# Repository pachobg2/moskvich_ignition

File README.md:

# moskvich_ignition — programmable ignition ECU for the Moskvich 412 / 2140

ESP32-C3 replaces the points-and-coil ignition's *switching* job while keeping
the original distributor. The points become a crank-position sensor, the ECU
fires the coil through an IGBT at a timing it looks up from an **rpm × MAP
map**, controls dwell from battery voltage, trims idle speed with spark
timing, and limits revs. Everything is tuned from a phone over the ECU's own
WiFi network — no app to install, no router needed.

> **Experimental, safety-relevant.** Wrong spark timing can wreck an engine,
> and a dead ECU means a dead engine (see *Limitations*). Bench-test with the
> simulator, verify timing with a timing light before every first start, and
> start from the conservative default map.

## How it works

```
 12 V switched ──┬── protection + buck ──► ESP32-C3 ──► gate ──► IGBT ──► coil (−)
                 │                           ▲  ▲
 distributor ────┼── pull-up + NPN ──────────┘  │ ADC
   (points)      │                              │
 MAP hose ───────┴── MPX4115-class sensor ──────┘
```

* **Trigger reference (Setup):** two choices.
  **OPEN edge (default)** — distributor locked at full advance, trigger ≈ 40°: most accurate.
  **CLOSE edge** — factory distributor (weights blocked at rest, vacuum capsule off), trigger ≈ 120°
  before the firing cylinder: the ECU predicts ~3× further ahead (use *Acceleration compensation*
  100%, which the UI sets for you), and while cranking it falls back to the OPEN edge (≈10° factory
  static timing) because 120° of prediction is far too coarse at cranking-speed variation.
  Host-simulated error: ≤0.04° steady, ~0.9° over a 1000→5500 rpm/4 s ramp, ≤0.5° on a hard
  lift-off with compensation, ≈0.3° cranking. The closing edge bounces more than the opening one:
  verify on a scope.
* **Points = sensor only.** They no longer carry coil current (no arcing, no
  condenser needed). The instant they *open* marks a fixed crank angle,
  `trigger angle` (≈ 40° BTDC).
* **The distributor's mechanical advance is locked at that angle** (weights
  blocked, vacuum capsule disconnected). The ECU can only *delay* the spark
  relative to the trigger, so any advance up to the trigger angle is
  available:
  `delay = (trigger − target advance) / 180° × time since last trigger`.
* **Dwell** is ECU-controlled and voltage-compensated: at idle/cranking the
  coil is switched on `delay − dwell` after the trigger (exact dwell); at
  higher rpm it is scheduled one cycle ahead from the measured period.
* **Timing map**: 16 rpm × 16 MAP bins, bilinear interpolation, ± idle trim,
  rev-limit retard, slew limit per spark, min/max clamps.
* **LPG**: a 12 V signal from the LPG valve (GPIO3 via divider) switches the
  timing. Two modes (LPG tab): **static offset** (petrol map + N degrees,
  default +3°; no map is shown) or a **separate LPG map** (edited on the LPG tab, with
  *Copy petrol → LPG* and an optional offset). The change is slewed in at the normal per-spark limit,
  never stepped. A *Force petrol / Force LPG* override in Setup helps testing without
  the valve connected (LPG tab).
* **Factory-derived maps (Map tab → "Ignition map")**: besides your *Custom* map there are three
  slots built from the distributor data tables of the UZAM-412 family — **P-147A**, **47.3706**,
  **P-147B** — so the engine can run on a replica of the original advance curve and you can tune from there.
  Total advance = static timing + centrifugal(rpm) + vacuum(MAP) × fade(rpm), using the data-sheet
  centrifugal points (1000–5000 rpm) and the vacuum-capsule points (mmHg). Assumptions: the static
  timing is 10° (editable, "Regenerate"); the tables are in crank degrees; vacuum = 101.3 kPa − MAP;
  the capsule's tolerance bands are used at their middle; the capsule is fed from a *ported* carburettor
  vacuum that is ~0 at idle, so the vacuum advance fades in between 900 and 1300 rpm; centrifugal advance
  starts at 600 rpm and stays at its 5000 rpm value above that. **The curves reach 50–60°**, so the
  trigger angle and *Maximum advance* must allow it (the CLOSE-edge reference at ≈120° does; a 30–40° trigger
  clips them — the app shows how many cells are clipped and hatches them). You can edit a factory slot;
  *Regenerate* restores its factory curve and *Copy to Custom* starts a tune from it.
* **Cranking** uses a fixed retarded advance below `crank rpm`.
* **Rev limiter**: retard ramp from the soft limit, spark cut above the hard limit.
* **Idle control**: PI loop that nudges timing to hold the target idle rpm
  while the throttle is closed (MAP below a threshold).
* **Ignition ISRs run at interrupt priority 3**, above WiFi, so tuning on a
  phone does not move the spark. Flash writes (saving, OTA) *do* stall them,
  so the ECU **refuses to write flash while the engine turns** — edits apply
  live and are saved when you press Save with the engine stopped, or
  automatically when it stops.
* Hardware safeguards in firmware: coil-on watchdog (9 ms) if no spark was
  scheduled, no spark without a valid period measurement, bounce rejection,
  all inputs from the web app clamped by `sanitize()`.

## Files

| File | Purpose |
|---|---|
| `moskvich_ignition.ino` | setup/loop: ADC sampling, idle PI, LED, WiFi AP, OTA |
| `ignition_core.h` | **all ignition math & scheduling** — pure C++, no Arduino; tested on a PC |
| `ecu_engine.h` | ESP32-C3 layer: GPIO ISR, two one-shot hardware timers, bench simulator |
| `ecu_store.h` | NVS persistence (checksummed) and parameter `sanitize()` |
| `ecu_web.h` | web server + JSON API |
| `web/index.html` | the tuning app (single file, no dependencies; add `?mock` to try it on a PC) |
| `web_ui.h` | generated from `web/index.html` by `python tools/embed_ui.py` |
| `test/test_core.cpp` | engine-model simulation of the real ISR logic |
| `config.h.example` | copy to `config.h`: AP/OTA passwords, pins, sensor constants (gitignored) |
| `docs/HARDWARE.md` | circuit, parts list, wiring, install & tuning procedure |
| `hardware/` | **schematic, PCB (KiCad), BOM** — through-hole, ESP32-C3-Zero, IGBT cut-out; see `hardware/README.md` |

## Build

Arduino IDE / arduino-cli, **esp32 core 3.x**, board *ESP32C3 Dev Module*
(*USB CDC On Boot: Enabled* for the SuperMini), library **ArduinoJson 7**.

```bash
arduino-cli compile --fqbn esp32:esp32:esp32c3:CDCOnBoot=cdc .
```

Copy `config.h.example` → `config.h` and set the passwords. After editing
`web/index.html` run `python tools/embed_ui.py`.

Host tests (any C++17 compiler):

```bash
c++ -O2 -std=c++17 -I. test/test_core.cpp -o test/test_core && ./test/test_core
```

## Using it

1. Join WiFi **Moskvich-ECU** (password from `config.h`); the app opens as a
   captive portal, or browse to `http://192.168.4.1`.
2. **Live** — rpm, advance, MAP, battery, dwell, 60 s chart.
3. **Map** — petrol map: tap cells, ±0.5/±1, Set, Smooth, Range select, Undo, editable axes.
   The cells around the current operating point glow while the engine runs.
4. **Setup** — trigger angle, cranking, idle, limits, dwell table, MAP sensor two-point calibration.
   **LPG** — mode, static offset or the separate LPG map, valve-signal status, override.
5. **Language** — the **БГ / EN** button in the header switches the whole interface between Bulgarian and English (remembered per browser; `?lang=bg` in the URL also works). The default follows the browser language. Translations live in the `BG` table in `web/index.html`; the firmware-upload page is bilingual.
6. **Tools** — timing-light lock, bench simulator, JSON backup/restore, reset, firmware update.

Install, wiring and the timing-light calibration procedure are in
[docs/HARDWARE.md](docs/HARDWARE.md).

## Limitations / ideas

* **No limp-home.** With advance locked at 40°, running the stock points
  circuit would kick back on starting, so there is no relay bypass. Carry a
  spare ECU or the original distributor internals.
* No cam/phase signal: cylinder-to-cylinder cam-lobe and bushing wear shows up as
  a few degrees of scatter that the ECU cannot correct. A Hall-effect or
  optical distributor conversion would use the same input (set the edge).
* No knock sensor, no coolant/air temperature correction (spare ADC pins exist).
* ISR jitter vs. WiFi has been reasoned about, not scope-measured: verify with a
  scope/timing light at 6000 rpm on the bench simulator and adjust `latency_us`.
* Idea: log a short ring buffer of rpm/MAP/advance for download after a drive.

## Version History

| Version | Date | Changes |
|---|---|---|
| 1.0.0 | 2026-10-26 | Initial release: points-trigger delay-only timing, 16×16 rpm×MAP map, voltage-compensated dwell, cranking/idle/rev-limit logic, WiFi AP web tuner (live data, map editor, setup, timing-light lock, bench simulator, backup, OTA), host-side engine-model tests. |
| 1.1.0 | 2026-10-27 | MAP sensor two-point calibration in Setup (any linear 1-bar analog sensor, e.g. GM/Lada/Bosch; capture-from-live-reading buttons); `MAP_SLOPE`/`MAP_OFFSET`/`MAP_SUPPLY_MV` removed from `config.h`. Stored settings from 1.0.0 are discarded on first boot (defaults load). |
| 1.2.0 | 2026-10-27 | LPG timing: 12 V valve-signal input (GPIO3, hysteresis + debounce), static-offset mode or separate LPG map, copy petrol → LPG (+offset), manual override, LPG badge in the UI. Settings from 1.1.0 are discarded on first boot (defaults load). |
| 1.2.1 | 2026-10-27 | UI: LPG settings moved to their own tab; the LPG map is only shown in "Separate LPG map" mode (static-offset mode shows just the offset). |
| 1.3.0 | 2026-10-27 | Setup: choice of trigger reference — points OPEN edge (distributor locked at full advance, ~40°) or points CLOSE edge (factory distributor, ~120°) with automatic OPEN-edge cranking reference; trigger angle range up to 160°; extended host tests. Settings from 1.2.x are discarded on first boot (defaults load). |
| 1.4.0 | 2026-10-27 | Web interface available in Bulgarian (БГ/EN switch, default from browser language), bilingual firmware-upload page; fix: elements marked hidden (e.g. the LPG copy button on the petrol map) were still shown. |
| 1.4.1 | 2026-10-27 | UI: hover tooltips (in both languages) on every setting and control, e.g. what Gain (P) and Gain (I) do; the web page is now stored gzip-compressed (flash use 92% -> 88%). |
| 1.5.0 | 2026-10-27 | Targets the ESP32-C3-Zero board (new PCB in `hardware/`): pins LPG 0 / MAP 1 / VBAT 3 / POINTS 4 / COIL 6, status shown on the on-board RGB LED (GPIO10). |
| 1.6.0 | 2026-10-28 | Three factory-derived petrol maps (P-147A, 47.3706, P-147B) selectable in the Map tab, built from the UZAM-412 distributor centrifugal + vacuum advance tables; regenerate / copy-to-custom; map cells may exceed the trigger angle (clipped at use, shown in the UI). Settings from 1.5.0 are discarded on first boot (defaults load). |
| 1.6.1 | 2026-10-28 | UI: switching the trigger reference to CLOSE edge now also raises Maximum advance to 60° (it was still capping the map at 38°); the "cells exceed the limit" warning names the limit that is binding (Maximum advance or Trigger angle) and where to change it. |
| 1.6.2 | 2026-10-28 | Safety: firmware updates are refused while the engine runs (a bare POST to /update no longer reboots the ECU, and ArduinoOTA is not serviced while running); /update reports OK only after a completed upload. |

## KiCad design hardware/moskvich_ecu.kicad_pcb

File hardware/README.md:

# ECU hardware — schematic, PCB, BOM (rev B, SMD)

A small two-sided board: **SMD** passives and ICs (0603 / 0805 / 1206 / 1210, SOT-23, SOIC-16, SMA/SMB), an
**SMD buck regulator** for the 5 V rail, an **ESP32-C3-Zero** on pin sockets, 3.5 mm screw terminals, and the
ignition **IGBT lying in a cut-out** so the case floor cools it. **48 × 41.8 mm** (about a third of the
through-hole rev A).

| File | What it is |
|---|---|
| `schematic.svg` | One-sheet schematic (open in any browser) |
| `pcb_top.svg`, `pcb_bottom.svg` | Board previews (both copper layers, courtyards, cut-out) |
| `moskvich_ecu.kicad_sch` | **Editable schematic**, KiCad 7 format (every pin has a net label; no hand-routed wires). Its netlist is checked identical to the PCB's. |
| `moskvich_ecu.kicad_pro` | Minimal KiCad project so the schematic and PCB open together |
| `moskvich_ecu.kicad_pcb` | The PCB, KiCad 7 format (footprints embedded, tracks, vias, GND pours, outline + cut-out) |
| `bom.csv`, `netlist.csv` | Parts list and net list |
| `gen/pcbgen.py` | Generator: parts, placement, auto-router, design-rule check, KiCad/SVG/BOM export |
| `gen/gen_schematic.py` | Draws `schematic.svg` (the readable picture) |
| `gen/gen_kicad_sch.py` | Writes `moskvich_ecu.kicad_sch` and verifies it against the PCB netlist |

Regenerate everything (needs `numpy scipy shapely`):

```bash
python hardware/gen/pcbgen.py && python hardware/gen/gen_schematic.py && python hardware/gen/gen_kicad_sch.py
```

> **Status — read this.** The board was generated and checked by my own script: copper clearance ≥ 0.2 mm
> (≥ 0.7 mm around the coil net), every net connected, nothing within 0.5 mm of the edge or inside the
> cut-out, no footprint overlaps, no hole collisions. The file parses in a KiCad-format library.
> **It has not been opened in KiCad, run through KiCad's DRC, or built.** The footprints are generic
> IPC-style land patterns I defined, not manufacturer drawings. Before ordering: open it in KiCad ≥ 7, press
> **B** to fill the zones, run **Inspect → Design Rules Checker**, and compare every footprint with the
> datasheet of the exact part you buy (especially the inductor, the fuse, the terminals and the module).

## Opening it in KiCad or EasyEDA

* **KiCad 7+:** open `moskvich_ecu.kicad_pro`. The schematic uses simple embedded symbols (boxes with named pins) and
  the footprint names of the PCB; reassign footprints/symbols to library parts as you like, then *Update PCB from schematic*.
* **EasyEDA:** import the files through EasyEDA's KiCad import (File → Import; menu names differ between the
  Standard and Pro editions — I have not tried it here). Import the schematic and the PCB; if the editor
  complains, open them in KiCad first and re-export. Replace the generic footprints with EasyEDA/LCSC library parts
  (this also gives JLCPCB assembly part numbers).
* The schematic is a **grouped parts-and-nets drawing**: connections are carried by net labels, not long wires.
  `schematic.svg` is the readable hand-arranged picture of the same circuit.
* Neither file was opened in KiCad/EasyEDA by me; the script re-reads the schematic and checks every pin's net
  against the PCB netlist (42 symbols, 24 nets, no mismatches).

## Circuit in one paragraph

Ignition-switched 12 V → 0.5 A fuse → SS34 Schottky (reverse polarity) → SMBJ24A TVS → 10 µF → **AP63205**
buck (3.8–32 V in, fixed 5 V, 2 A; L = 4.7 µH, 2 × 22 µF out, 100 nF boot — the datasheet's values) → 5 V. The
points signal (J1.1) is pulled up through 1 kΩ (wetting current), divided and inverted by a BC847 into GPIO4.
The LPG valve signal, the battery voltage and the MAP sensor each go through a divider with a 100 nF cap and
a 3.6 V zener into ADC1 pins. The MCU's coil command (GPIO6) feeds a **CD74HCT221** monostable that (a) turns the 3.3 V
logic into a 5 V gate drive and (b) limits coil-on time in hardware (≈ 16–23 ms with the 15 kΩ / 2.2 µF
network; the firmware limits it to 9 ms first), so a hung MCU can never leave the coil charged. It drives the
**ISL9V3040P3** ignition IGBT; its collector (the tab) is the coil negative (J1.4). Coil current never flows
through the buck or the sensor grounds: it uses the 1.5 mm top-layer collector track and the GND pours / J1.3.

## Board facts

* **48 × 41.8 mm**, 2 layers, 1.6 mm, three M2.5 mounting holes. Origin = top-left corner, X right, Y down (as in KiCad).
* Rules used: tracks 0.2 mm (signal) / 0.4 mm (power) / **1.5 mm** (collector), clearance 0.2 mm (0.7 mm around the collector net), vias 0.8 / 0.4 mm, GND pours on both layers. These are within normal 2-layer fab capabilities.
* **Top side:** module sockets, J1/J2, the IGBT pads, and the buck stage (U2, L1, C1–C4, C11, D1, D2, F1).
* **Bottom side:** everything else (dividers, points input, the CD74HCT221 and its resistors). The bottom parts sit in the 6 mm gap between the board and the case floor, so keep them ≤ 3 mm tall.
* **Terminals:** J2 (top right) = LPG signal, +5 V, MAP signal, GND. J1 (right) = points lead, +12 V, GND, coil −. The coil track and the GND pour handle the 4 A pulses; use ≥ 1 mm² wire on J1.3 / J1.4.
* The module's USB-C faces the **top** edge (2.2 mm from it).

## Mounting the IGBT through the cut-out

The IGBT is cooled by the **case floor**, which acts as the heat sink.

```
   box floor (aluminium) ─────────────────────────────  z = 0
        │     ┌ M3 screw into a tapped hole in the floor
   tab ─┴─ insulating pad (silicone, 0.25 mm) + shoulder washer
   TO-220 lies flat in the cut-out  ───►  leads bent UP through the 3 pads
   PCB on 6 mm standoffs  ─────────────────────────────  z = 6
```

* **Cut-out:** 18.0 × 13.0 mm window at x 3.64 … 21.64, y 27.79 … 40.79 (bottom-left of the board). The strip below it is only 1.0 mm wide — handle the board by the edges.
* **Lead pads** (Q1), 3.0 mm to the right of the window, 2.54 mm pitch, 1.0 mm drill: collector (24.64, 34.29), emitter (24.64, 31.75), gate (24.64, 36.83) — the part is rotated 180° compared with a part lying leads-left, so **the gate is the lowest pad**. The silkscreen outline shows the package.
* **Tab hole** ends up near (8.1, 34.3) (the board is the drilling template through the cut-out). Check against your real part before drilling the floor.
* **Lead forming:** leave ~4 mm flat from the package, bend up 90°, trim to just clear the board top.
* **The tab is the coil negative** (battery voltage plus spikes to ~400 V). Insulate it from the case: silicone pad + plastic shoulder washer under the screw head. Check with a multimeter that tab ↔ case is open before powering the board.
* Dissipation is ≈ 2–3 W at 6000 rpm (≈ 0.3 W at idle); the floor of a metal box is plenty. On a plastic box use a real heat sink bolted to the tab.
* Conformal-coat the board: the collector net sees ~400 V flyback spikes with only 0.7–0.8 mm clearance.

## Parts and where the numbers come from

| Item | Notes |
|---|---|
| **AP63205WU-7** (U2) | Pinout, 4.7 µH / 10 µF / 2 × 22 µF / 100 nF and "EN to VIN" are from the Diodes datasheet (DS41326). Abs. max VIN 35 V DC / 40 V for 400 ms — hence the SMBJ24A TVS (clamps ≈ 39 V). Fit enough ceramic capacitance after derating (X7R/X5R lose capacity with DC bias). |
| **L1** | Any shielded 4.7 µH inductor, I_sat ≥ 2 A, DCR < 100 mΩ, about 4 × 4 mm. The land pattern is generic: adjust it to your part. |
| **F1** | An SMD fuse (0.5 A, ≥ 32 V rating) or a PTC of the same 1206 size. Ordinary 1206 PTCs are often rated only 6–15 V: do not use those. |
| **C10 / R14** | 2.2 µF X7R + 15 kΩ ⇒ guard time ≈ 0.7·R·C (CD74HCT221 datasheet), with the capacitor derated by its DC bias: 16–23 ms. If you change them keep it above the firmware's 9 ms and below ~25 ms. |
| ESP32-C3-Zero pad order | Pad numbers/GPIOs follow the Waveshare list (1 = 5V, 2 = GND, 3 = 3V3, 4–9 = IO0…IO5 down the left side, 10–18 = IO6, IO7, IO8, IO9, IO10, IO18, IO19, IO20, IO21 up the right side, USB at the top). **Read the silkscreen on your module** and measure the header row distance (15.24 mm assumed). |
| Module antenna | I did not leave a copper-free zone under the module (SMD parts and pours sit under its body); check where the antenna is on your revision and, if needed, move parts and add a keep-out there. |
| MAP sensor connector | J2.2 +5 V, J2.3 signal, J2.4 GND. GM-style sensors are usually A = ground, B = signal, C = 5 V — check yours. |

## Bring-up

1. **Without** the module, the CD74HCT221 and the IGBT: power from a bench supply (current limit 0.3 A). Check +5 V, check reverse polarity is blocked, check the TVS does not conduct at 14.4 V.
2. Fit U3 and the module, flash, join `Moskvich-ECU`. LED: blue blip = stopped, yellow = cranking, green = petrol, cyan = LPG, violet = simulator / OTA.
3. Tools → Bench simulator at 800 / 3000 / 6000 rpm with a **100 Ω resistor and LED, or a scope, instead of the coil** on J1.4. Check one pulse per trigger and on-time = the dwell shown in the Live tab.
4. Hold the command high on purpose (firmware stopped, jumper 3.3 V → GPIO6): the CD74HCT221 output must drop after ≈ 16–23 ms.
5. Only then fit Q1, connect the coil and the distributor, and follow `docs/HARDWARE.md`.

## Not done / ideas

* No gerbers: export them from KiCad (File → Plot) after the DRC. Add a fab note and silk text.
* Hand-soldering: everything is 0603 or larger; the SOIC-16 and TSOT-23-6 need a fine tip and flux. Solder the buck IC and its caps first, then check the 5 V rail.
* A coil-current sense resistor and an IGBT over-current limit were left out to keep the build simple.
* Unused module pins on the left header (IO2, IO5) are unconnected — a coolant-temperature divider would use IO2 (ADC1).

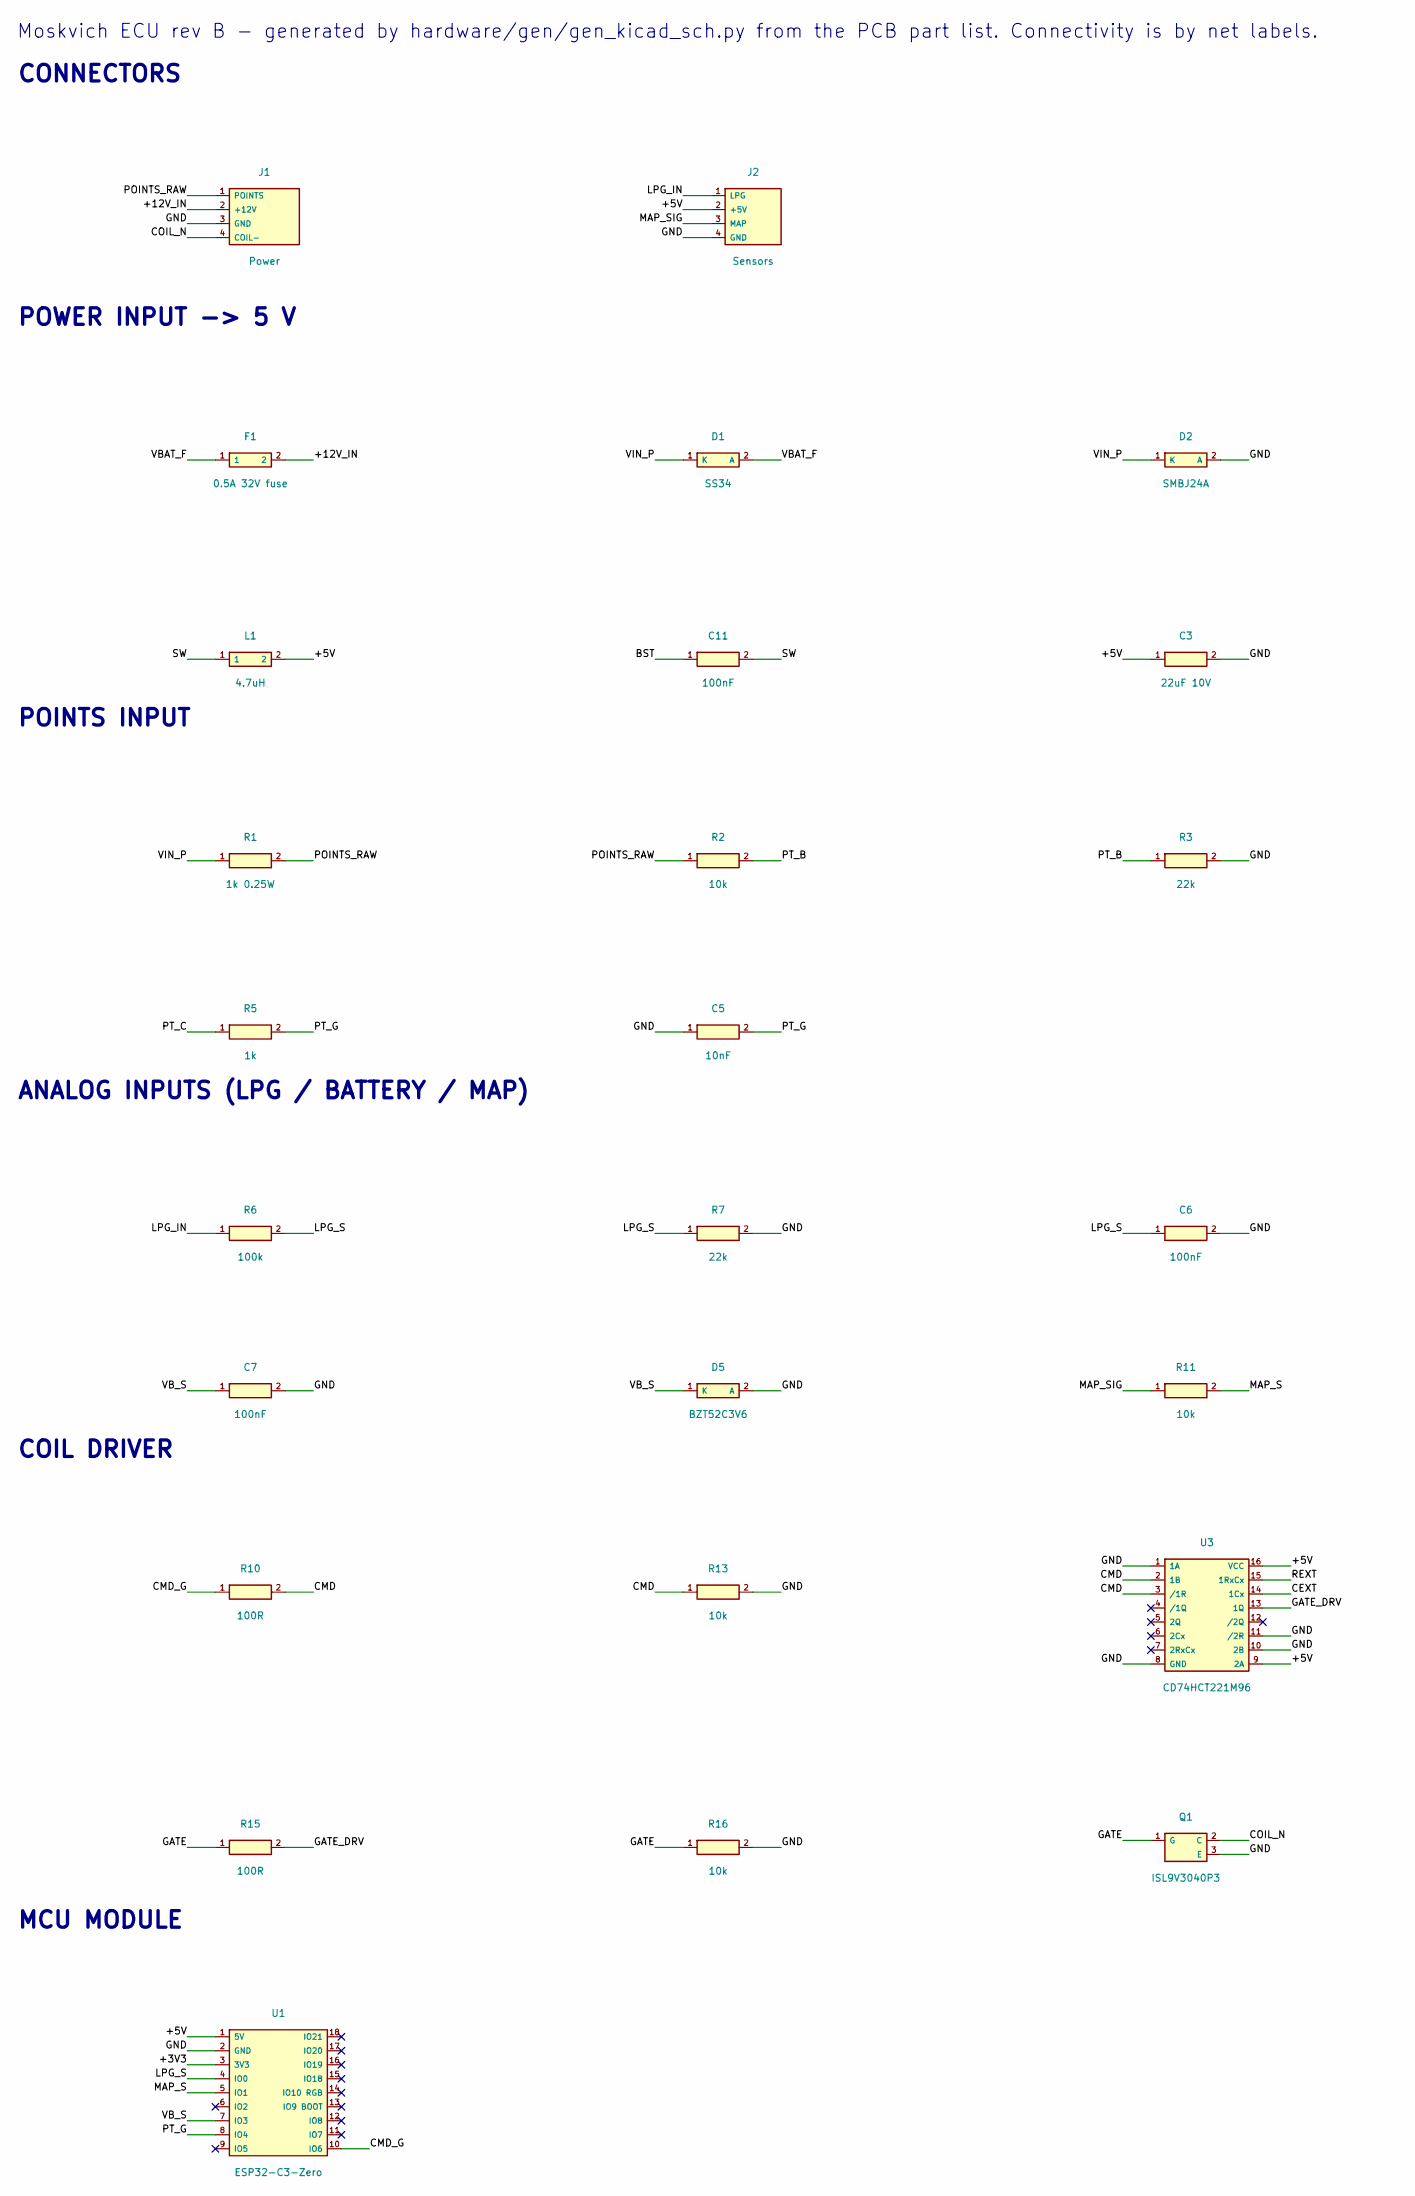
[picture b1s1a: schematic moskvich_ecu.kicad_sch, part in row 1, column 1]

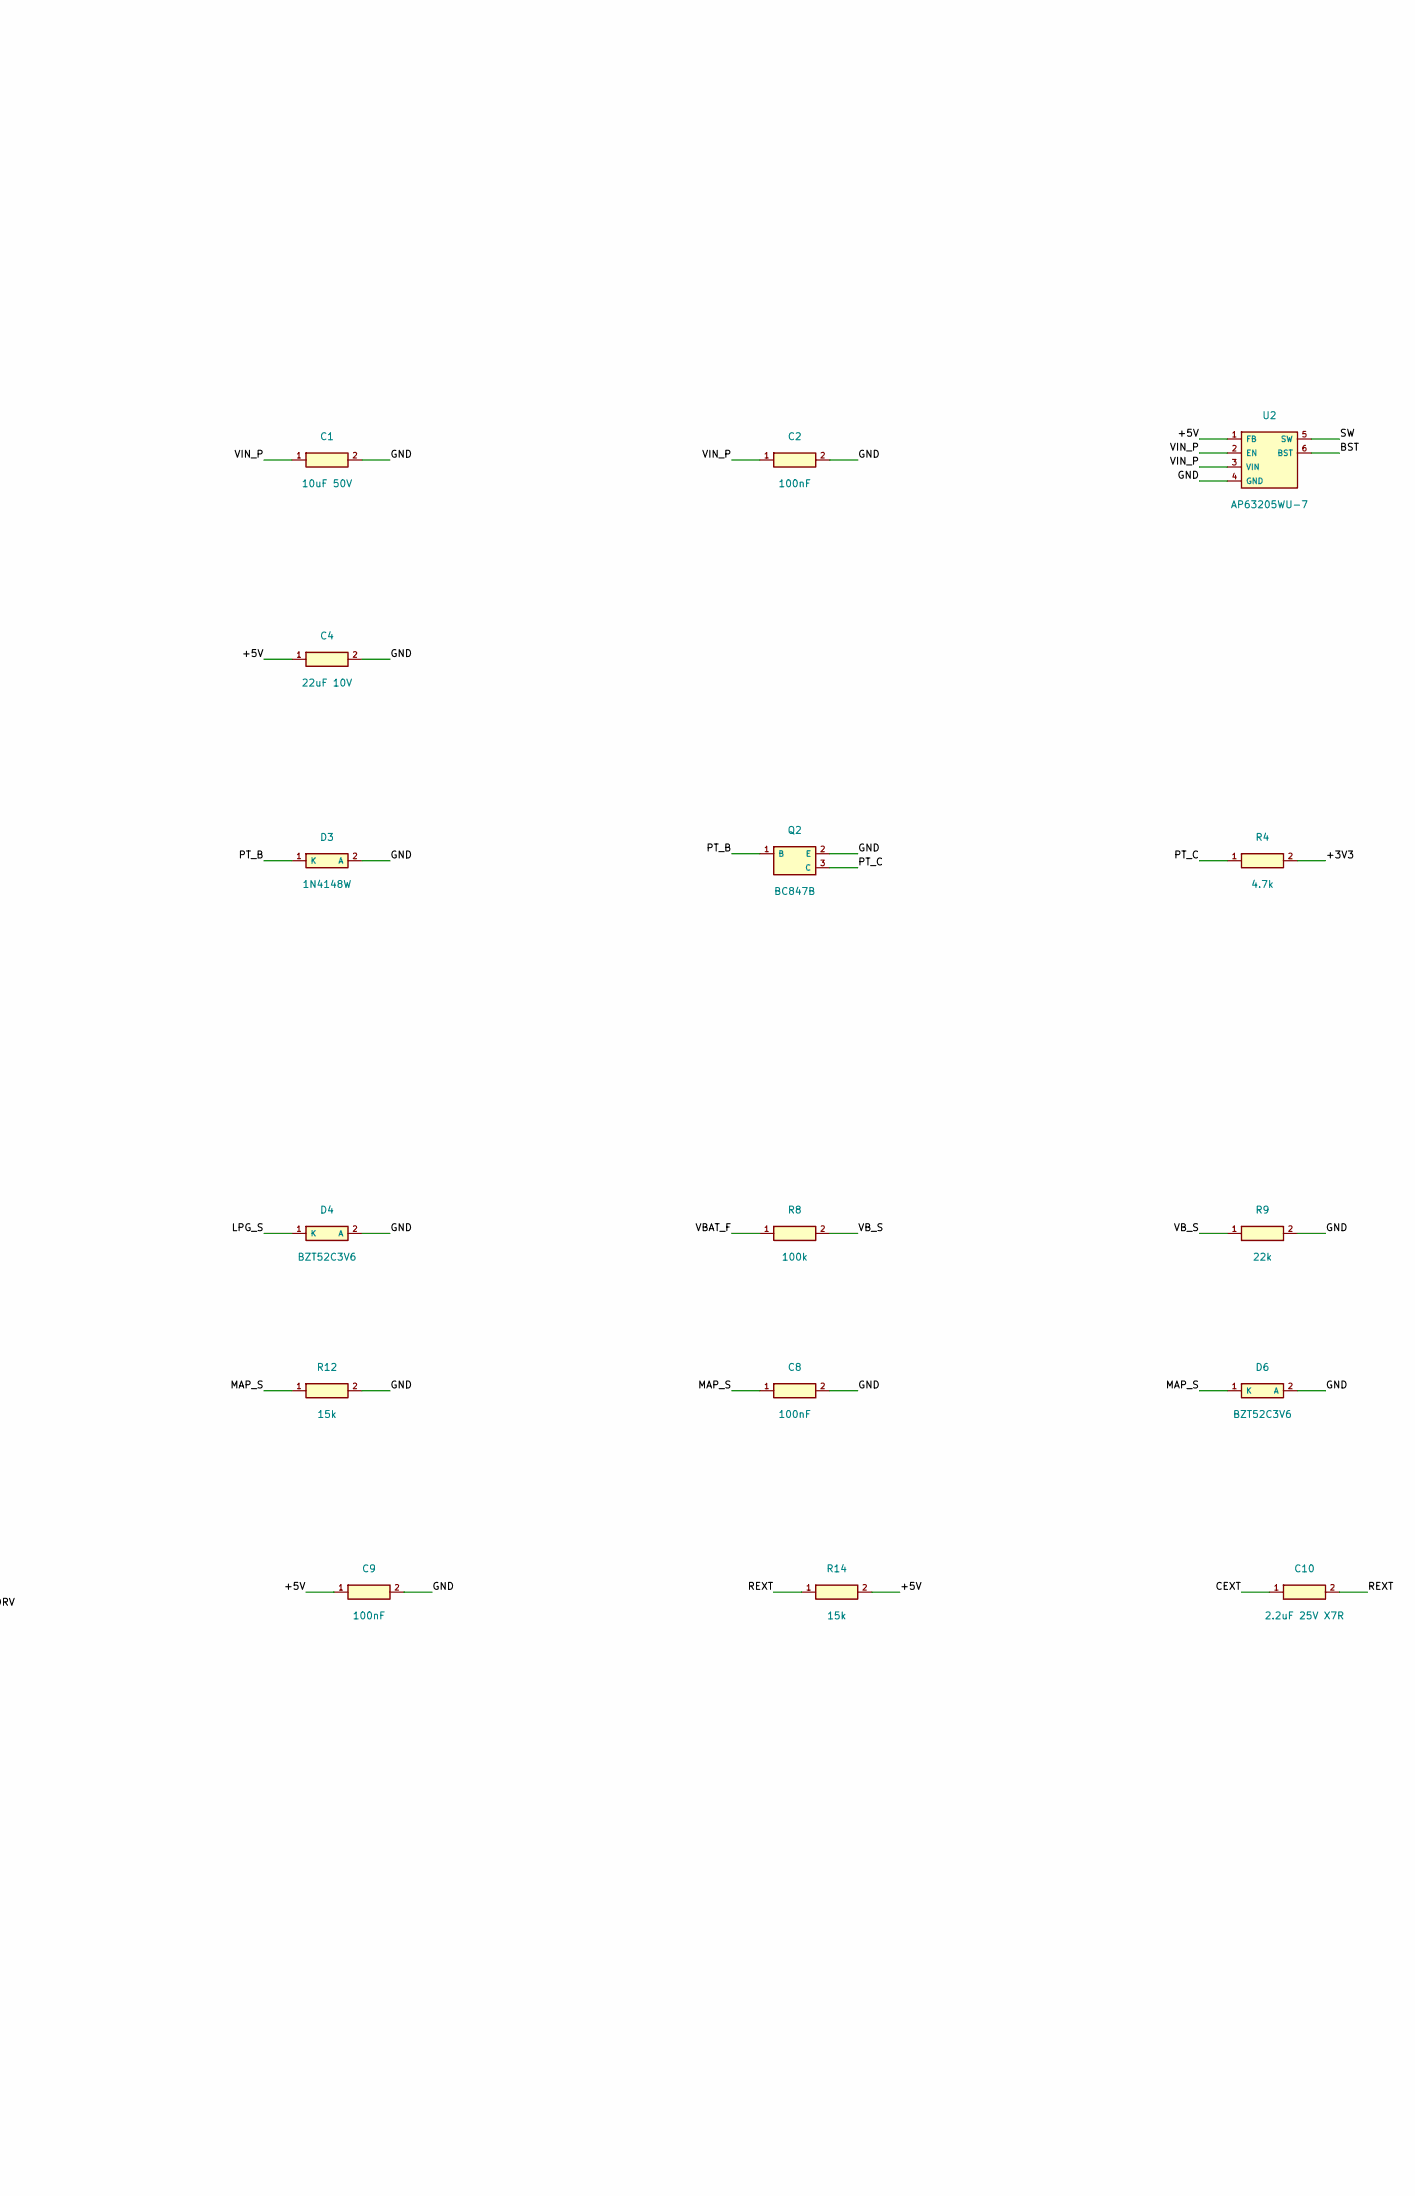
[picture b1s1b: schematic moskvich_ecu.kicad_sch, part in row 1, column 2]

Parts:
C1: 10uF 50V; C_1210_3225Metric
C2, C6, C7, C8, C9, C11: 100nF; C_0603_1608Metric
C3, C4: 22uF 10V; C_0805_2012Metric
C5: 10nF; C_0603_1608Metric
C10: 2.2uF 25V X7R; C_0805_2012Metric
D1: SS34; D_SMA
D2: SMBJ24A; D_SMB
D3: 1N4148W; D_SOD-123
D4, D5, D6: BZT52C3V6; D_SOD-123
F1: 0.5A 32V fuse; Fuse_1206_3216Metric
J1: Power; TerminalBlock_P3.50_1x04
J2: Sensors; TerminalBlock_P3.50_1x04
L1: 4.7uH; pick your inductor)
Q1: ISL9V3040P3; TO-220_LayDown_Cutout
Q2: BC847B; SOT-23
R1: 1k 0.25W; R_1206_3216Metric
R2, R11, R13, R16: 10k; R_0603_1608Metric
R3, R7, R9: 22k; R_0603_1608Metric
R4: 4.7k; R_0603_1608Metric
R5: 1k; R_0603_1608Metric
R6, R8: 100k; R_0603_1608Metric
R10, R15: 100R; R_0603_1608Metric
R12, R14: 15k; R_0603_1608Metric
U1: ESP32-C3-Zero; ESP32-C3-Zero_2x9_Socket
U2: AP63205WU-7; SOT-23-6
U3: CD74HCT221M96; SOIC-16_3.9x9.9mm_P1.27mm

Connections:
+3V3: R4.2, U1.3 (3V3)
+5V: C3.1, C4.1, C9.1, J2.2 (+5V), L1.2, R14.2, U1.1 (5V), U2.1 (FB), U3.9 (2A), U3.16 (VCC)
+12V_IN: F1.2, J1.2 (+12V)
BST: C11.1, U2.6 (BST)
CEXT: C10.1, U3.14 (1Cx)
CMD: R10.2, R13.1, U3.2 (1B), U3.3 (/1R)
CMD_G: R10.1, U1.10 (IO6)
COIL_N: J1.4 (COIL-), Q1.2 (C)
GATE: Q1.1 (G), R15.1, R16.1
GATE_DRV: R15.2, U3.13 (1Q)
GND: C1.2, C2.2, C3.2, C4.2, C5.1, C6.2, C7.2, C8.2, C9.2, D2.2 (A), D3.2 (A), D4.2 (A), D5.2 (A), D6.2 (A), J1.3 (GND), J2.4 (GND), Q1.3 (E), Q2.2 (E), R3.2, R7.2, R9.2, R12.2, R13.2, R16.2, U1.2 (GND), U2.4 (GND), U3.1 (1A), U3.8 (GND), U3.10 (2B), U3.11 (/2R)
LPG_IN: J2.1 (LPG), R6.1
LPG_S: C6.1, D4.1 (K), R6.2, R7.1, U1.4 (IO0)
MAP_S: C8.1, D6.1 (K), R11.2, R12.1, U1.5 (IO1)
MAP_SIG: J2.3 (MAP), R11.1
POINTS_RAW: J1.1 (POINTS), R1.2, R2.1
PT_B: D3.1 (K), Q2.1 (B), R2.2, R3.1
PT_C: Q2.3 (C), R4.1, R5.1
PT_G: C5.2, R5.2, U1.8 (IO4)
REXT: C10.2, R14.1, U3.15 (1RxCx)
SW: C11.2, L1.1, U2.5 (SW)
VBAT_F: D1.2 (A), F1.1, R8.1
VB_S: C7.1, D5.1 (K), R8.2, R9.1, U1.7 (IO3)
VIN_P: C1.1, C2.1, D1.1 (K), D2.1 (K), R1.1, U2.2 (EN), U2.3 (VIN)

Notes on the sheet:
CONNECTORS
POWER INPUT -> 5 V
POINTS INPUT
ANALOG INPUTS (LPG / BATTERY / MAP)
COIL DRIVER
MCU MODULE
Moskvich ECU rev B - generated by hardware/gen/gen_kicad_sch.py from the PCB part list. Connectivity is by net labels.

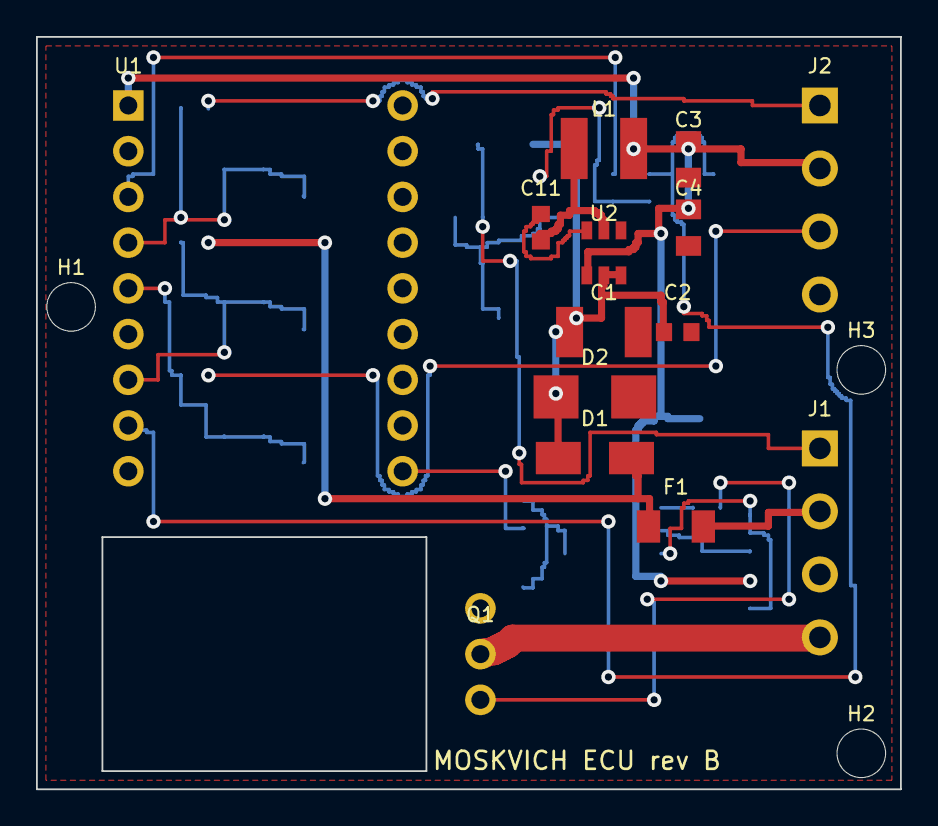
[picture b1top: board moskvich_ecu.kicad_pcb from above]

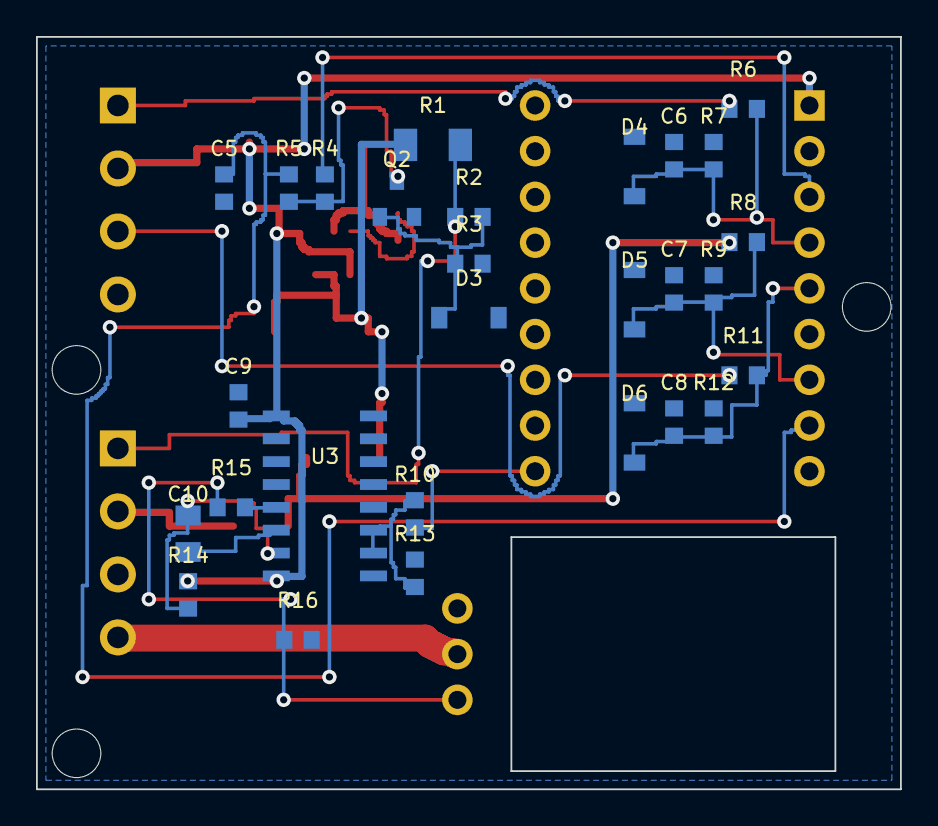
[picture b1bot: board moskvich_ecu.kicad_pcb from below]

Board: 2 copper layers, 48.0 x 41.8 mm, 45 parts (28 on the bottom side), 24 nets.

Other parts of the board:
H1, H2, H3: M2.5; MountingHole_2.7_M2.5

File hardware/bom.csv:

Qty,Refs,Value,Footprint,Description
1,C1,10uF 50V,C_1210,Capacitor 1210 X7R 10 uF 50 V
1,C10,2.2uF 25V X7R,C_0805,"Capacitor 0805 X5R/X7R (22 uF >= 10 V, 2.2 uF >= 25 V)"
6,C11 C2 C6 C7 C8 C9,100nF,C_0603,Capacitor 0603 X7R 50 V
2,C3 C4,22uF 10V,C_0805,"Capacitor 0805 X5R/X7R (22 uF >= 10 V, 2.2 uF >= 25 V)"
1,C5,10nF,C_0603,Capacitor 0603 X7R 50 V
1,D1,SS34,D_SMA,Schottky SMA (pin 1 = cathode)
1,D2,SMBJ24A,D_SMB,"TVS SMB, unidirectional (pin 1 = cathode)"
1,D3,1N4148W,D_SOD-123,SOD-123 diode (pin 1 = cathode)
3,D4 D5 D6,BZT52C3V6,D_SOD-123,SOD-123 diode (pin 1 = cathode)
1,F1,0.5A 32V fuse,Fuse_1206,"SMD fuse 0.5 A, rated >= 32 V (1206 / 2410), or a resettable PTC of the same footprint"
3,H1 H2 H3,M2.5 mounting hole (6 mm standoff),MountingHole_2.7_M2.5,M2.5 screw + 6 mm standoff
1,J1,Power,TerminalBlock_P3.50_1x04,"Screw terminal 3.5 mm pitch, 4 positions, 8 A"
1,J2,Sensors,TerminalBlock_P3.50_1x04,"Screw terminal 3.5 mm pitch, 4 positions, 8 A"
1,L1,4.7uH,L_4x4,"Shielded power inductor 4.7 uH, 4x4 mm, I_sat >= 2 A, DCR < 100 mOhm (check the land pattern of the part you buy)"
1,Q1,ISL9V3040P3,TO-220_LayDown_Cutout,"Ignition IGBT ISL9V3040P3 (TO-220), laid flat on the case floor in the cut-out"
1,Q2,BC847B,SOT-23,"NPN BC847B (1 = B, 2 = E, 3 = C)"
1,R1,1k 0.25W,R_1206,"Resistor 1206, 0.25 W"
2,R10 R15,100R,R_0603,Resistor 0603 1 % (thick film)
4,R11 R13 R16 R2,10k,R_0603,Resistor 0603 1 % (thick film)
2,R12 R14,15k,R_0603,Resistor 0603 1 % (thick film)
1,R4,4.7k,R_0603,Resistor 0603 1 % (thick film)
1,R5,1k,R_0603,Resistor 0603 1 % (thick film)
2,R6 R8,100k,R_0603,Resistor 0603 1 % (thick film)
3,R3 R7 R9,22k,R_0603,Resistor 0603 1 % (thick film)
1,U1,ESP32-C3-Zero,ESP32-C3-Zero_2x9_Socket,"Waveshare ESP32-C3-Zero on 2x 1x9 female headers (2.54 mm, 15.24 mm apart)"
1,U2,AP63205WU-7,SOT-23-6,"AP63205WU-7 (TSOT-26): 1 FB, 2 EN, 3 VIN, 4 GND, 5 SW, 6 BST"
1,U3,CD74HCT221M96,SOIC-16_3.9x9.9mm_P1.27mm,"CD74HCT221M96 (SOIC-16 narrow; same pinout as the 74HCT123). Non-retriggerable, tW = 0.7 Rx Cx"

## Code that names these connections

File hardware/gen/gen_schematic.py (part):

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

def igbt(x, y, ref, val):
    """gate pin (x,y); collector pin (x+42,y-40); emitter pin (x+42,y+40)"""
    add(f'<g stroke="{INK}" stroke-width="1.8" fill="none" stroke-linecap="round"><path d="M{x},{y} H{x + 12} M{x + 12},{y - 16} V{y + 16}"/>'
        f'<path d="M{x + 20},{y - 18} V{y + 18} M{x + 20},{y - 11} H{x + 42} V{y - 40} M{x + 20},{y + 11} H{x + 42} V{y + 40}"/>'
        f'<path d="M{x + 33},{y + 6} L{x + 42},{y + 11} L{x + 33},{y + 16} Z" fill="{INK}"/></g>')
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
# =================================================================== connectors
block(20, 80, 250, 560, "CONNECTORS")
for (y0, ref, sub, pins) in ((120, "J1", "Power / coil / points", ["POINTS_RAW", "+12V_IN", "GND", "COIL_N"]),
                             (390, "J2", "Sensors", ["LPG_IN", "+5V", "MAP_SIG", "GND"])):
    box(36, y0, 80, 168, fill="#eef4ff")
    text(76, y0 + 20, ref, 14, "middle", bold=True); text(76, y0 + 36, sub[:14], 10, "middle", italic=True)
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sym("F", bx + 120, ry, "h", "F1", "0.5A 32V fuse", 76)
nA = bx + 230
wire(bx + 196, ry, nA, ry); dot(nA, ry)
wire(nA, ry, nA, ry - 44); netlabel(nA, ry - 44, "VBAT_F (to R8)")
sym("D", nA + 20, ry, "h", "D1", "SS34", 64)
wire(nA, ry, nA + 20, ry)
nB = bx + 380
wire(nA + 84, ry, nB, ry); dot(nB, ry)
text(nB + 10, ry + 20, "VIN_P", 11.5, c=NETC, bold=True)
sym("R", nB, ry - 100, "v", "R1", "1k 0.25W", 56)
wire(nB, ry - 44, nB, ry); netlabel(nB, ry - 100, "POINTS_RAW") if False else None
wire(nB, ry - 100, nB, ry - 112); netlabel(nB, ry - 112, "POINTS_RAW")
xs = [nB + 110, nB + 220, nB + 310]
wire(nB, ry, xs[2], ry)
sym("T", xs[0], ry, "v", "D2", "SMBJ24A TVS", 64, rev=True); dot(xs[0], ry); gnd(xs[0], ry + 64)
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
# =================================================================== points
py = 610
block(bx, py, 900, 340, "POINTS INPUT   (points open ⇒ PT_G / GPIO4 goes LOW)")
y = py + 190
netlabel(bx + 14, y, "POINTS_RAW"); wire(bx + 110, y, bx + 130, y)
sym("R", bx + 130, y, "h", "R2", "10k", 64)
n1 = bx + 250
wire(bx + 194, y, n1, y); dot(n1, y); text(n1 - 6, y - 18, "PT_B", 11.5, "end", c=NETC, bold=True)
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n3 = r5 + 120
wire(r5 + 64, yc, n3 + 60, yc); dot(n3, yc)
sym("C", n3, yc, "v", "C5", "10nF", 64); gnd(n3, yc + 64)
netlabel(n3 + 60, yc, "PT_G → U1 pad 8")
text(bx + 14, py + 300, "R1 (above) gives ≈12 mA wetting current through the points. The BC847 inverts, so points open ⇒ PT_C low.", 11, c="#555")
text(bx + 14, py + 317, "R5 + C5 form a 10 µs filter; the firmware also rejects contact bounce. D3 clamps negative spikes at the base.", 11, c="#555")

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    wire(n3, y, n3 + 60, y); netlabel(n3 + 60, y, outl)


divider(170, "LPG_IN", "R6", "100k", "R7", "22k", "C6", "D4", "LPG_S", "→ U1 pad 4 (GPIO0)")
divider(320, "VBAT_F", "R8", "100k", "R9", "22k", "C7", "D5", "VB_S", "→ U1 pad 7 (GPIO3)")
divider(470, "MAP_SIG", "R11", "10k", "R12", "15k", "C8", "D6", "MAP_S", "→ U1 pad 5 (GPIO1)")
text(cx + 14, 580, "3.6 V zeners protect the pins from wiring faults.  VBAT 12 V → 2.2 V,  LPG ≥ 7 V = on / ≤ 4 V = off,  MAP 4.8 V → 2.9 V.", 11, c="#555")
text(cx + 14, 597, "MAP sensor: any linear 5 V 1-bar analog type (e.g. GM-style), calibrated with the two-point tool in the web app.", 11, c="#555")

# =================================================================== coil driver
dy = 670
block(cx, dy, 1090, 500, "COIL DRIVER   — CD74HCT221 = on-time guard (≈ 20 ms) + 5 V gate drive")
netlabel(cx + 14, dy + 190, "CMD_G")
wire(cx + 96, dy + 190, cx + 120, dy + 190)
sym("R", cx + 120, dy + 190, "h", "R10", "100R", 64)
nc_ = cx + 240
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sym("R", ng, gy, "v", "R16", "10k", 60); gnd(ng, gy + 60)
Qi = igbt(ng + 50, gy, "Q1", "ISL9V3040P3")
wire(ng, gy, ng + 50, gy)
wire(Qi[1][0], Qi[1][1], Qi[1][0], Qi[1][1] - 14); netlabel(Qi[1][0], Qi[1][1] - 14, "COIL_N")
gnd(Qi[2][0], Qi[2][1])
nx_ = cx + 780
text(nx_, dy + 400, "Q1: TO-220 lies flat on the case floor, tab insulated", 11.5, c="#333", bold=True)
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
